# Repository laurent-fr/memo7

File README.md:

# memo7
A DIY MEMO7 cartridge for the TO7-70 computer

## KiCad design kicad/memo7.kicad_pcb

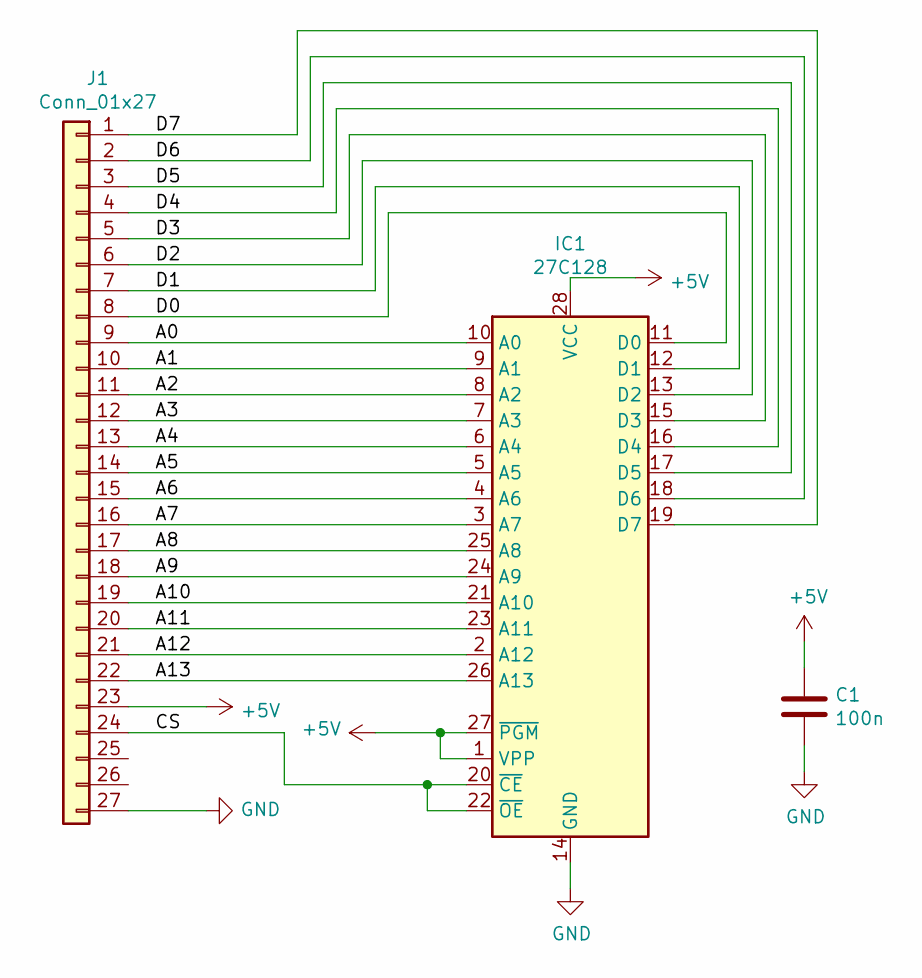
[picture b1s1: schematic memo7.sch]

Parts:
C1: 100n; CAP-2-HEX
IC1: 27C128; DIL-28
J1: Conn_01x27; CONN_MEMO7

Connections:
+5V: C1.1, IC1.1 (VPP), IC1.27 (~PGM), IC1.28 (VCC), J1.23
/A0: IC1.10 (A0), J1.9
/A1: IC1.9 (A1), J1.10
/A2: IC1.8 (A2), J1.11
/A3: IC1.7 (A3), J1.12
/A4: IC1.6 (A4), J1.13
/A5: IC1.5 (A5), J1.14
/A6: IC1.4 (A6), J1.15
/A7: IC1.3 (A7), J1.16
/A8: IC1.25 (A8), J1.17
/A9: IC1.24 (A9), J1.18
/A10: IC1.21 (A10), J1.19
/A11: IC1.23 (A11), J1.20
/A12: IC1.2 (A12), J1.21
/A13: IC1.26 (A13), J1.22
/CS: IC1.20 (~CE), IC1.22 (~OE), J1.24
/D0: IC1.11 (D0), J1.8
/D1: IC1.12 (D1), J1.7
/D2: IC1.13 (D2), J1.6
/D3: IC1.15 (D3), J1.5
/D4: IC1.16 (D4), J1.4
/D5: IC1.17 (D5), J1.3
/D6: IC1.18 (D6), J1.2
/D7: IC1.19 (D7), J1.1
GND: C1.2, IC1.14 (GND), J1.27

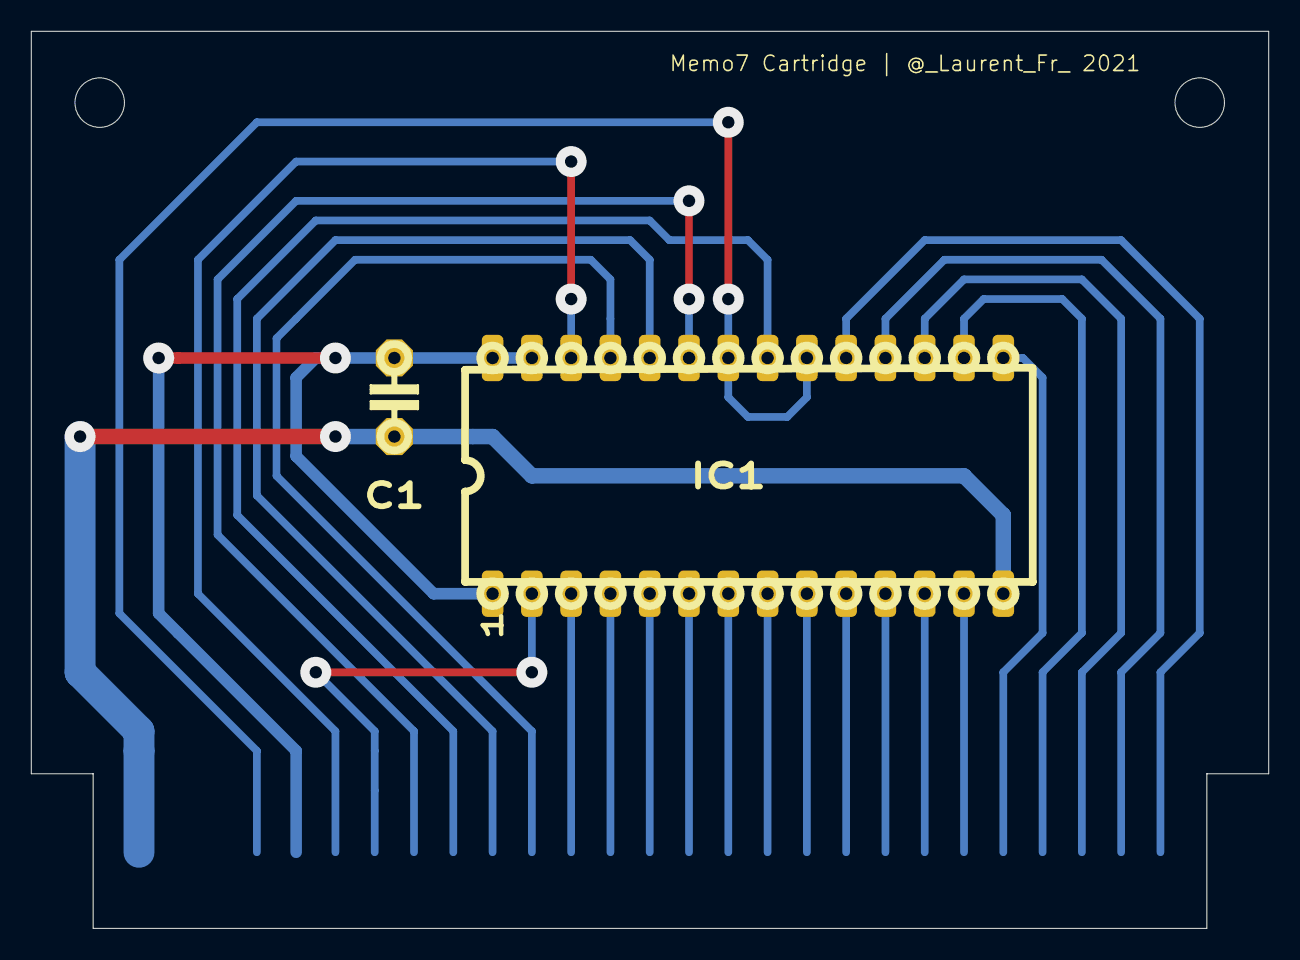
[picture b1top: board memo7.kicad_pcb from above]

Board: 2 copper layers, 80.0 x 58.0 mm, 3 parts (1 on the bottom side), 25 nets.
